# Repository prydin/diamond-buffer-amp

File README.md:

# A very simple diamond buffer audio amplifier

*** WORK IN PROGRESS ***

## Abstract
This design is based on an idea by the user `No ideas` (yes, that's really his handle) at diyaudio.com. It's a very simple design based 
on an opamp (NE5532 in this case) and a diamond buffer. It has not yet been built, but it's showing promising performance in simulations. 
Check back for more details once a prototype has been built!

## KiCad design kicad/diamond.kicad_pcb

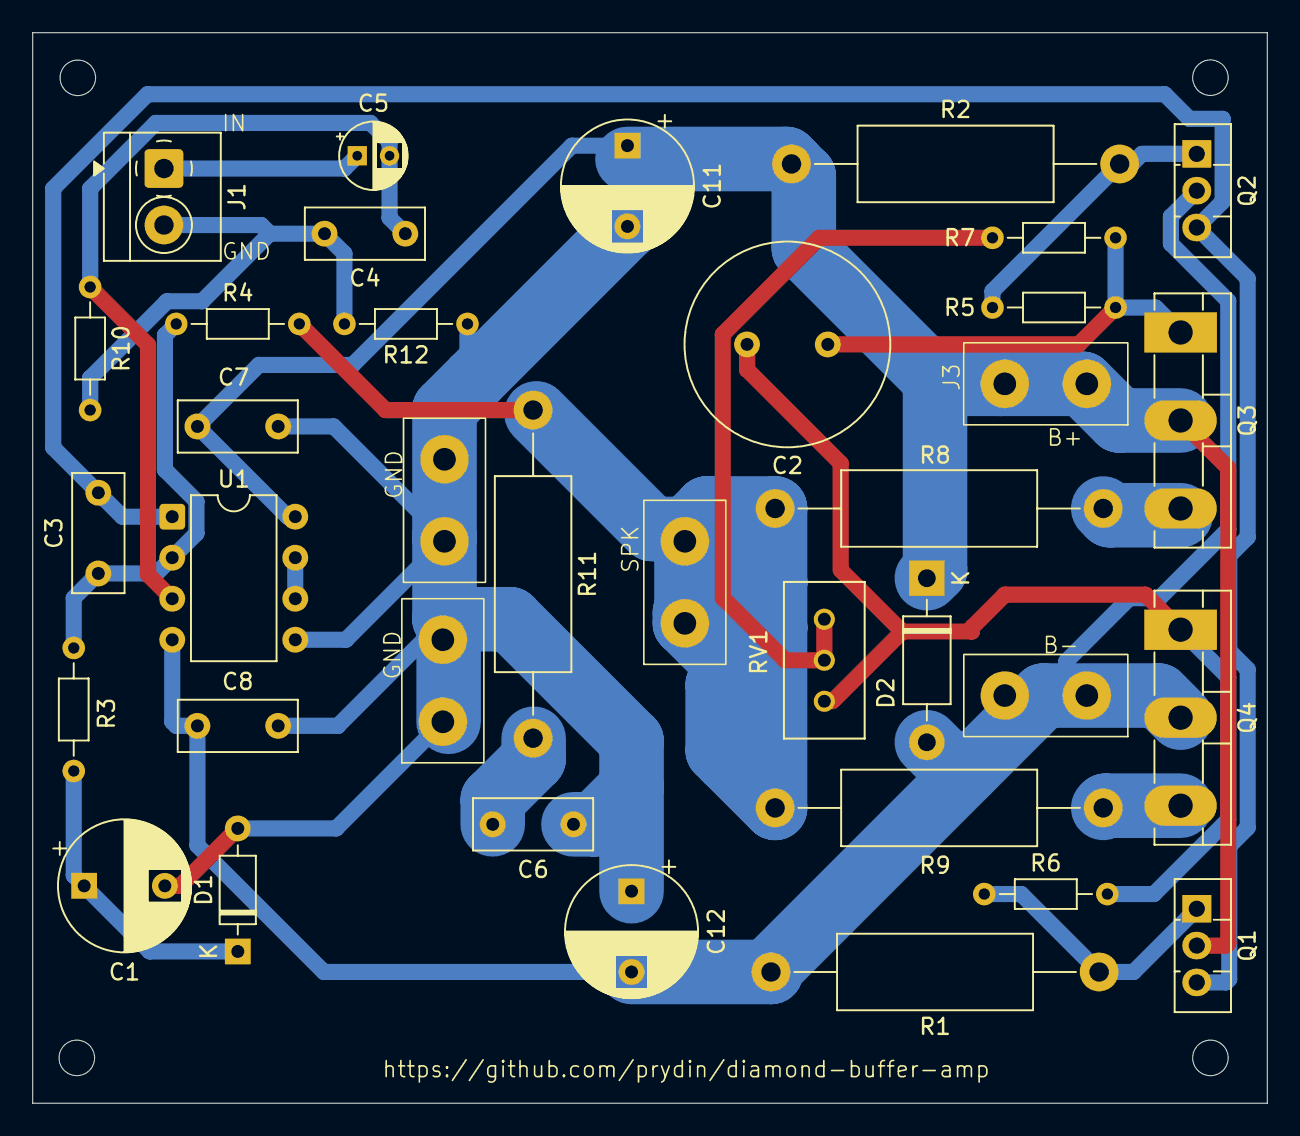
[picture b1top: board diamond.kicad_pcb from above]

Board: 2 copper layers, 76.5 x 66.3 mm, 36 parts (0 on the bottom side), 19 nets.

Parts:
C1: 220u; CP_Radial_D8.0mm_P5.00mm
C2: 1000u; C_Radial_D12.5mm_H20.0mm_P5.00mm
C3: 22p; C_Rect_L7.2mm_W3.0mm_P5.00mm_FKS2_FKP2_MKS2_MKP2
C4: 220p; C_Rect_L7.2mm_W3.0mm_P5.00mm_FKS2_FKP2_MKS2_MKP2
C5: 4.7u; CP_Radial_D4.0mm_P2.00mm
C6, C7, C8: 100n; C_Rect_L7.2mm_W3.0mm_P5.00mm_FKS2_FKP2_MKS2_MKP2
C11, C12: 100u; CP_Radial_D8.0mm_P5.00mm
D1: 1N4148; D_DO-35_SOD27_P7.62mm_Horizontal
D2: 1N4004; D_DO-41_SOD81_P10.16mm_Horizontal
J1: INPUT; TerminalBlock_4Ucon_1x02_P3.50mm_Horizontal
J2, J3, J4, J5, J6: Spade Connector
Q1: BD139; TO-126-3_Vertical
Q2: BD140; TO-126-3_Vertical
Q3: NJW0281G; TO-3P-3_Vertical
Q4: NJW0302G; TO-3P-3_Vertical
R1, R2: 1.5k; R_Axial_DIN0414_L11.9mm_D4.5mm_P20.32mm_Horizontal
R3: 1k; R_Axial_DIN0204_L3.6mm_D1.6mm_P7.62mm_Horizontal
R4: 10k; R_Axial_DIN0204_L3.6mm_D1.6mm_P7.62mm_Horizontal
R5, R6: 10; R_Axial_DIN0204_L3.6mm_D1.6mm_P7.62mm_Horizontal
R7: 470; R_Axial_DIN0204_L3.6mm_D1.6mm_P7.62mm_Horizontal
R8, R9: 0.5; R_Axial_DIN0414_L11.9mm_D4.5mm_P20.32mm_Horizontal
R10: 47k; R_Axial_DIN0204_L3.6mm_D1.6mm_P7.62mm_Horizontal
R11: 10; R_Axial_DIN0414_L11.9mm_D4.5mm_P20.32mm_Horizontal
R12: 100; R_Axial_DIN0204_L3.6mm_D1.6mm_P7.62mm_Horizontal
RV1: 1k; TRIM_T93YA103KT20
U1: NE5532; DIP-8_W7.62mm

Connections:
B+: C7.1, C11.1, D2.1 (K), J3.1, J3.2, Q1.2 (C), Q3.2 (B), R2.1, U1.8 (V+)
B-: C8.1, C12.2, D2.2 (A), J4.1, J4.2, Q2.2 (C), Q4.2 (C), R1.2, U1.4 (V-)
GND: C1.2, C6.2, C7.2, C8.2, C11.2, C12.1, D1.2 (A), J5.1, J5.2, J6.1, J6.2, R12.1, U1.5 (+)
GNDS: C4.2, J1.2, R10.2, R12.2
IN: C5.1, J1.1
unnamed: C6.1, R11.2
unnamed: C1.1, D1.1 (K), R3.1
unnamed: C3.2, Q1.3 (B), Q2.3 (B), U1.1
unnamed: Q1.1 (E), R1.1, R6.1
unnamed: Q2.1 (E), R2.2, R5.1
unnamed: C2.1, Q3.1 (C), R5.2, R7.1
unnamed: Q3.3 (E), R8.1
unnamed: C2.2, Q4.1 (B), R6.2, RV1.3
unnamed: Q4.3 (E), R9.2
unnamed: R7.2, RV1.1, RV1.2
unnamed: C4.1, C5.2, R10.1, U1.3 (+)
unnamed: C3.1, R3.2, R4.1, U1.2 (-)
unnamed: U1.6 (-), U1.7
SPK: J2.1, J2.2, R4.2, R8.2, R9.1, R11.1

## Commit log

2025-04-03 Cleanup
2025-04-03 Added gerber
2025-04-03 Small adjustment
